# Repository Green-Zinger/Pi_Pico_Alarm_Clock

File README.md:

# Pi_Pico_Alarm_Clock
This is a alarm clock using a LCD screen, a ds3231 module, and a pi pico.

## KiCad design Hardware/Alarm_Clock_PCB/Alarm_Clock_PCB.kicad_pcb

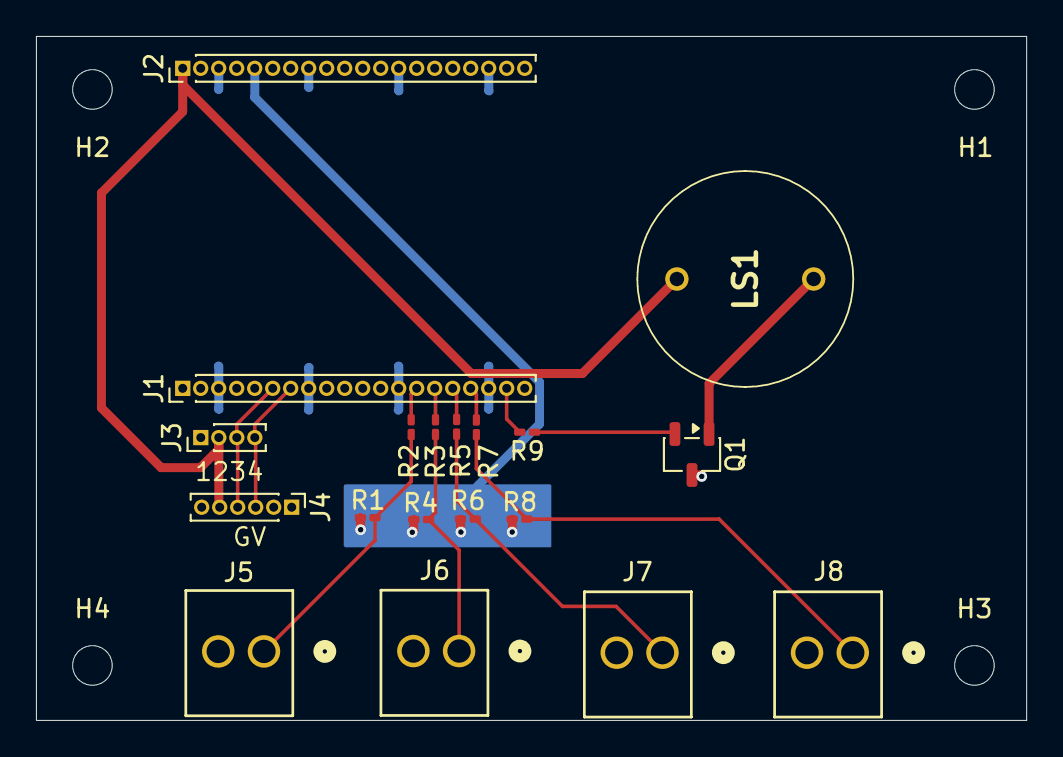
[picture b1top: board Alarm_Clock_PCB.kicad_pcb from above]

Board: 2 copper layers, 55.0 x 38.0 mm, 23 parts (0 on the bottom side), 16 nets.

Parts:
H1, H2, H3, H4: MountingHole; MountingHole_2.2mm_M2
J1, J2: Conn_01x20_Socket; PinHeader_1x20_P1.00mm_Vertical
J3: Conn_01x04_Socket; PinHeader_1x04_P1.00mm_Vertical
J4: Conn_01x06_Socket; PinHeader_1x06_P1.00mm_Vertical
J5, J6, J7, J8: Screw_Terminal_01x02; CONN_OSTVN02A150_OST
LS1: TMB12A05
Q1: NMOS; SOT-23-3
R1, R2, R3, R4, R5, R6, R7, R8: 10k; R_0201_0603Metric_Pad0.64x0.40mm_HandSolder
R9: 1k; R_0201_0603Metric_Pad0.64x0.40mm_HandSolder

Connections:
+3.3V: J2.5, R1.2, R4.2, R6.2, R8.2
GND: J1.3, J1.8, J1.13, J1.18, J2.3, J2.8, J2.13, J2.18, J3.1, J4.6, J5.2, J6.2, J7.2, J8.2, Q1.3 (S)
GP4: J1.6, J3.3, J4.4
GP5: J1.7, J3.4, J4.3
GP10: J1.14, R2.1
GP11: J1.15, R3.1
GP12: J1.16, R5.1
GP13: J1.17, R7.1
GP14: J1.19, R9.2
unnamed: J5.1, R1.1, R2.2
unnamed: J6.1, R3.2, R4.1
unnamed: J7.1, R5.2, R6.1
unnamed: J8.1, R7.2, R8.1
unnamed: LS1.2 (-), Q1.1 (D)
unnamed: Q1.2 (G), R9.1
VBUS: J2.1, J3.2, J4.5, LS1.1 (+)

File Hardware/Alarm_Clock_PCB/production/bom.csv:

Designator,Footprint,Quantity,Value,LCSC Part #
"J1, J2",PinHeader_1x20_P1.00mm_Vertical,2,Conn_01x20_Socket,
J3,PinHeader_1x04_P1.00mm_Vertical,1,Conn_01x04_Socket,
J4,PinHeader_1x06_P1.00mm_Vertical,1,Conn_01x06_Socket,
"J5, J6, J7, J8",CONN_OSTVN02A150_OST,4,Screw_Terminal_01x02,
LS1,TMB12A05,1,TMB12A05,
Q1,SOT-23-3,1,NMOS,
"R1, R2, R3, R4, R5, R6, R7, R8",0201,8,10k,
R9,0201,1,1k,
